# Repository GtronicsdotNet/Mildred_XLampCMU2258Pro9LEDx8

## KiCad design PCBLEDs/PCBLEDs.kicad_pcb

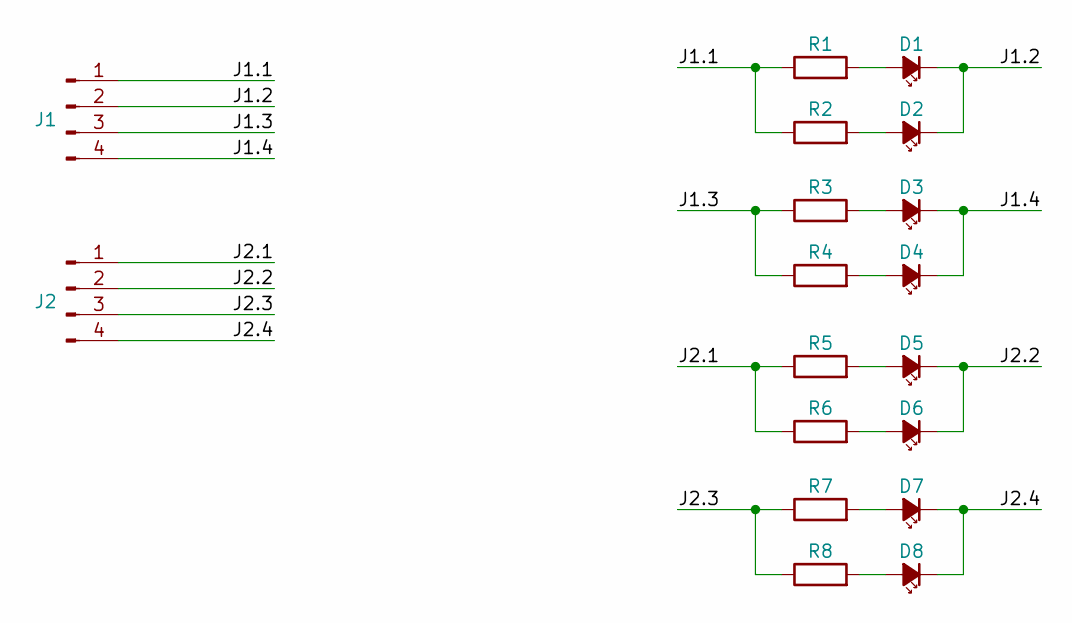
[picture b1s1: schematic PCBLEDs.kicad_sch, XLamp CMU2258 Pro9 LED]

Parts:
D1, D2, D3, D4, D5, D6, D7, D8: LED_Small_Filled; XLamp CMU2258 Pro9 LED
J1, J2: Conn_01x04_Pin; PhoenixContact_MSTBVA_2,5_4-G-5,08_1x04_P5.08mm_Vertical
R1, R2, R3, R4, R5, R6, R7, R8: R; R_2512_6332Metric_Pad1.40x3.35mm_HandSolder

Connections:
/J1.1: J1.1, R1.1, R2.1
/J1.2: D1.1 (K), D2.1 (K), J1.2
/J1.3: J1.3, R3.1, R4.1
/J1.4: D3.1 (K), D4.1 (K), J1.4
/J2.1: J2.1, R5.1, R6.1
/J2.2: D5.1 (K), D6.1 (K), J2.2
/J2.3: J2.3, R7.1, R8.1
/J2.4: D7.1 (K), D8.1 (K), J2.4
unnamed: D1.2 (A), R1.2
unnamed: D2.2 (A), R2.2
unnamed: D3.2 (A), R3.2
unnamed: D4.2 (A), R4.2
unnamed: D5.2 (A), R5.2
unnamed: D6.2 (A), R6.2
unnamed: D7.2 (A), R7.2
unnamed: D8.2 (A), R8.2

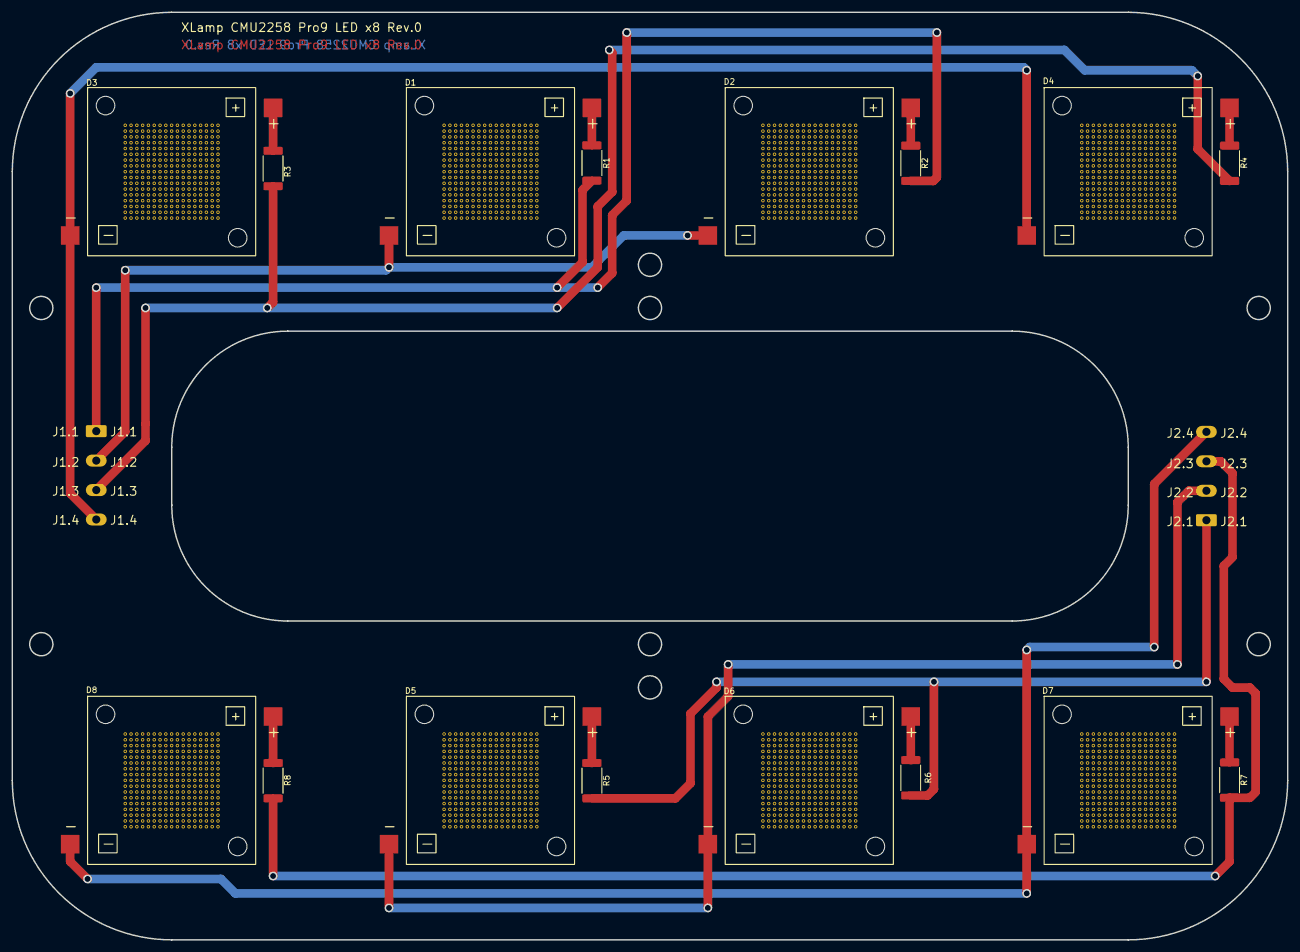
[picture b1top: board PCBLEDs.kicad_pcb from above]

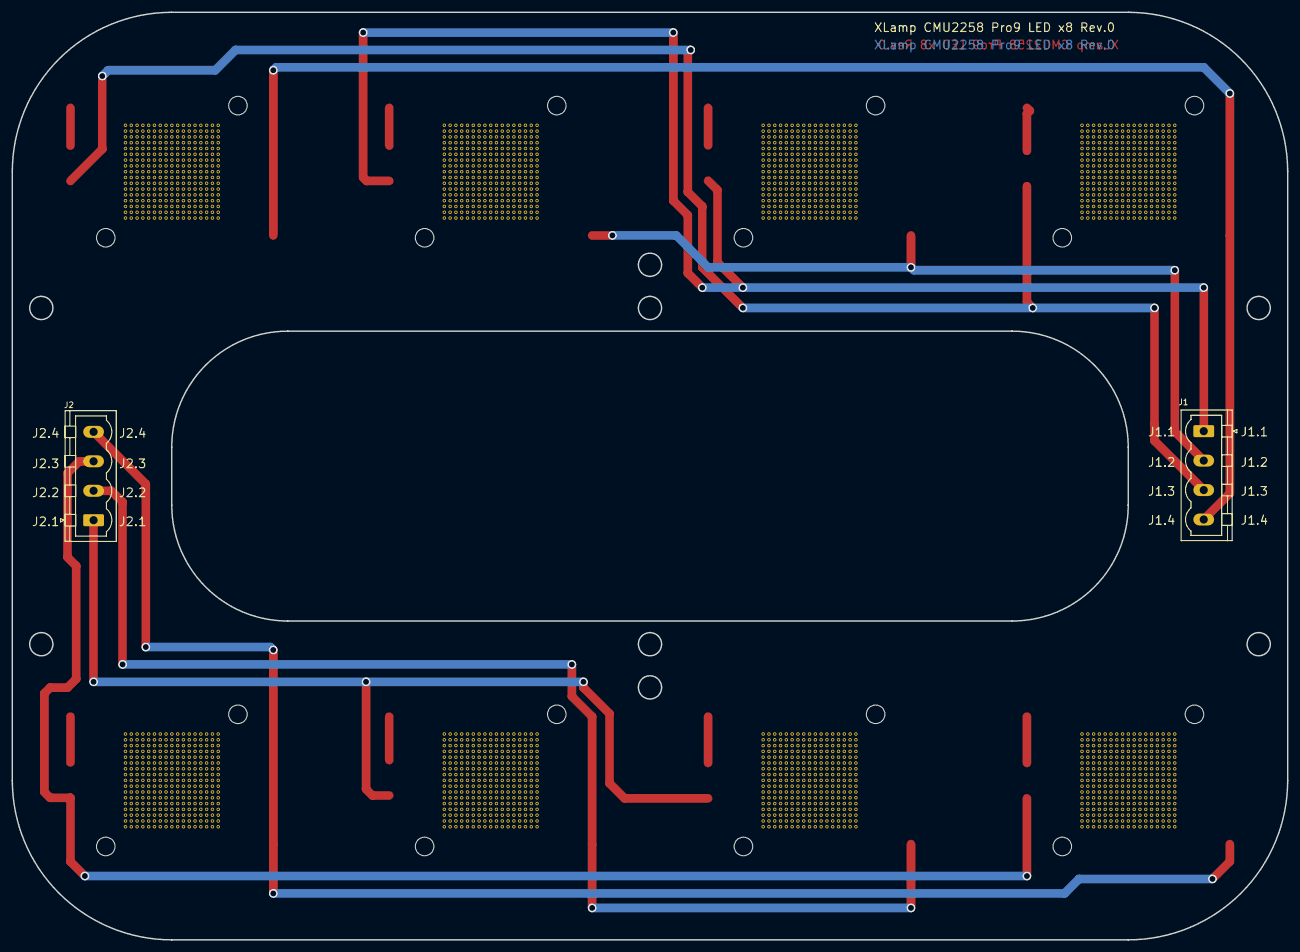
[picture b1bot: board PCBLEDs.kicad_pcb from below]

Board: 2 copper layers, 220.0 x 160.0 mm, 18 parts (2 on the bottom side), 16 nets.

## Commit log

2025-05-02 Primo commit
    eseguto dopo ordine a JLCPCB della Rev.0
